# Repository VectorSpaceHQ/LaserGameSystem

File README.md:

# LaserGameSystem
A laser projector system which plays video games.

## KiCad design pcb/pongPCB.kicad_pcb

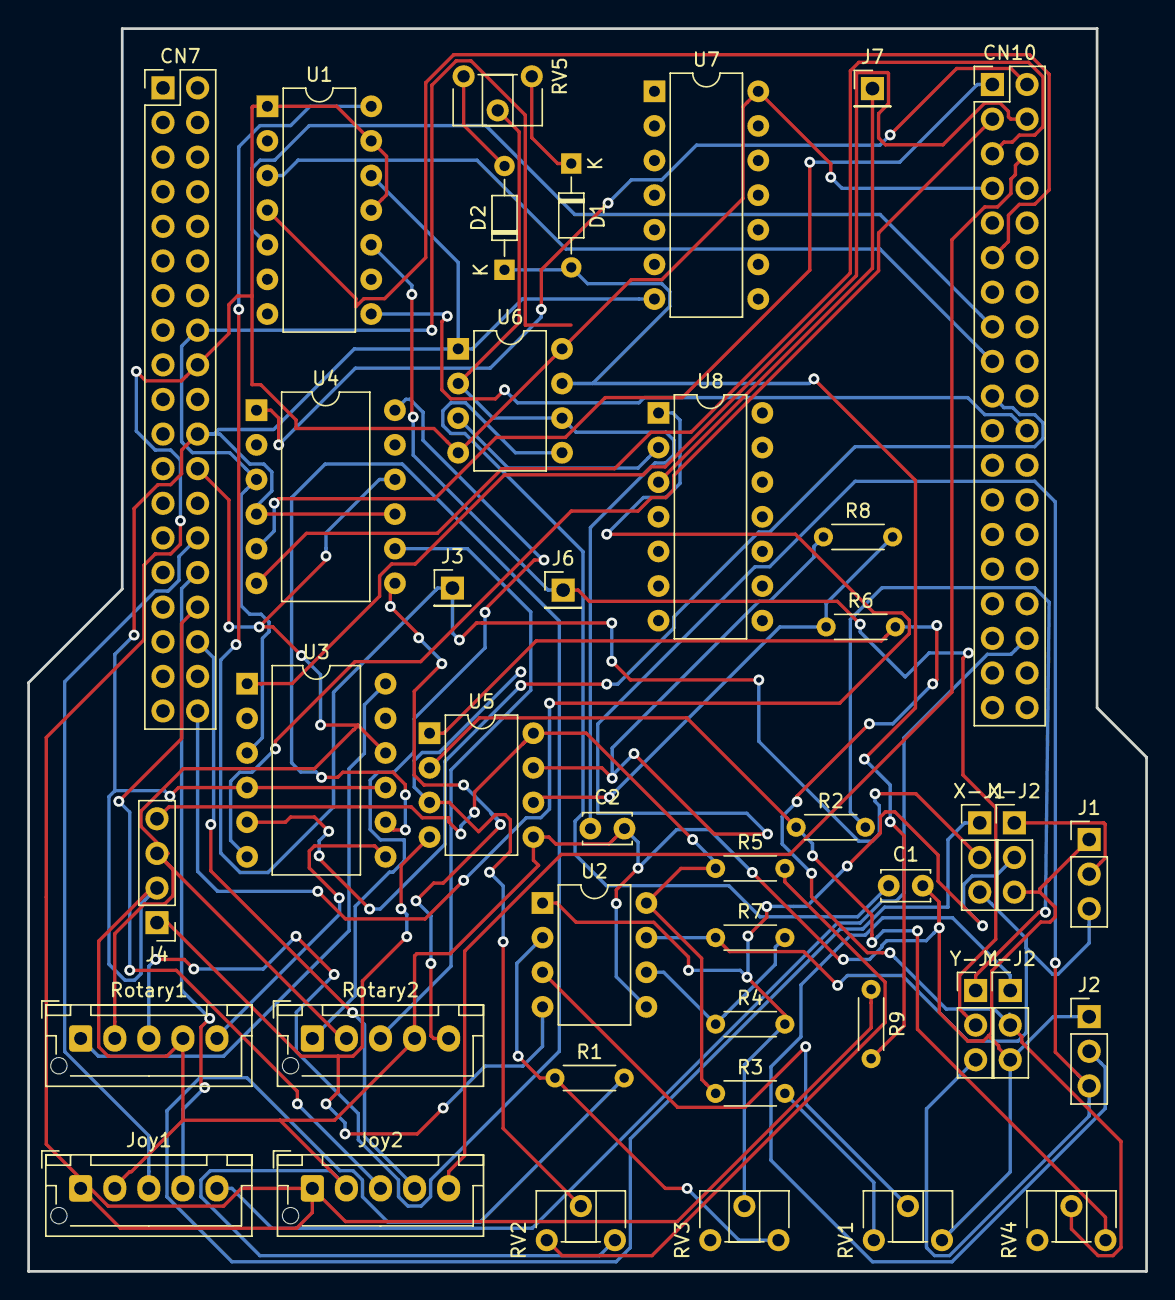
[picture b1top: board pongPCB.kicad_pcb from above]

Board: 2 copper layers, 82.0 x 91.2 mm, 42 parts (0 on the bottom side), 54 nets.

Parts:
C1: 104; C_Disc_D3.4mm_W2.1mm_P2.50mm
C2: 101; C_Disc_D3.4mm_W2.1mm_P2.50mm
CN7, CN10: Conn_02x19_Odd_Even; PinHeader_2x19_P2.54mm_Vertical
D1, D2: D; D_DO-34_SOD68_P7.62mm_Horizontal
J1: X_ILDA_OUT; PinHeader_1x03_P2.54mm_Vertical
J2: Y_ILDA_OUT; PinHeader_1x03_P2.54mm_Vertical
J3: Xprobe; PinHeader_1x01_P2.54mm_Vertical
J4: PowerInput; PinHeader_1x04_P2.54mm_Vertical
J6: Yprobe; PinHeader_1x01_P2.54mm_Vertical
J7: LaserToggle; PinHeader_1x01_P2.54mm_Vertical
Joy1, Joy2: Conn_01x05_Male; JST_XH_B05B-XH-AM_1x05_P2.50mm_Vertical
R1, R2: 1k; R_Axial_DIN0204_L3.6mm_D1.6mm_P5.08mm_Horizontal
R3, R5: 47k; R_Axial_DIN0204_L3.6mm_D1.6mm_P5.08mm_Horizontal
R4, R6, R7, R8: 10k; R_Axial_DIN0204_L3.6mm_D1.6mm_P5.08mm_Horizontal
R9: 2K; R_Axial_DIN0204_L3.6mm_D1.6mm_P5.08mm_Horizontal
RV1, RV2, RV3, RV4: 10k; Potentiometer_ACP_CA6-H2,5_Horizontal
RV5: 100K; Potentiometer_ACP_CA6-H2,5_Horizontal
Rotary1, Rotary2: Rotary_Encoder_Switch; JST_XH_B05B-XH-AM_1x05_P2.50mm_Vertical
U1: MCP4922; DIP-14_W7.62mm
U2, U5: TL082; DIP-8_W7.62mm
U3, U4: levelshift; DIP-12_W10.16mm
U6: NE555; DIP-8_W7.62mm
U7, U8: 4081; DIP-14_W7.62mm
X-J1: XJumper1; PinHeader_1x03_P2.54mm_Vertical
X-J2: XJumper2; PinHeader_1x03_P2.54mm_Vertical
Y-J1: YJumper1; PinHeader_1x03_P2.54mm_Vertical
Y-J2: YJumper2; PinHeader_1x03_P2.54mm_Vertical

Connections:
+3V3: CN7.16, U3.3, U4.3
+5V: CN7.18, CN10.7, Joy1.1, Joy2.1, R9.1, U1.1, U1.11, U1.13, U6.4, U6.8, U7.14
+12V: CN7.24, J4.3, Rotary1.2, Rotary2.2, U3.10, U4.10
+15V: J4.4, R3.1, R5.1, U2.8, U5.8
-15V: J4.1, U2.4, U5.4
/BUTTON1: CN10.3, U3.6
/BUTTON2: CN10.5, U4.6
/CLK1: CN10.19, U3.5
/CLK2: CN10.1, U4.5
/DT1: CN10.4, U3.1
/DT2: CN10.2, U4.1
/JOY1BUTTON: CN10.34, Joy1.5
/JOY1X: CN7.28, Joy1.3
/JOY1Y: CN7.30, Joy1.4
/JOY2BUTTON: CN10.6, Joy2.5
/JOY2X: CN7.32, Joy2.3
/JOY2Y: CN7.34, Joy2.4
/LASER_TOGGLE: CN7.38, U8.1
/LATCH: CN10.22, U1.8
GND: C1.2, C2.2, CN7.22, J1.1, J2.1, J4.2, Joy1.2, Joy2.2, RV1.3, RV2.3, Rotary1.4, Rotary2.4, U1.12, U2.5, U3.4, U3.9, U4.4, U4.9, U5.5, U6.1, U7.7, X-J2.3, Y-J2.3
unnamed: C1.1, U6.5
unnamed: C2.1, RV5.2, U6.2, U6.6
unnamed: CN10.11, U1.4
unnamed: CN10.15, U1.5
unnamed: CN10.17, U1.3
unnamed: D1.1, RV5.1
unnamed: D1.2, D2.1, R9.2, U6.7
unnamed: D2.2, RV5.3
unnamed: J1.2, X-J2.1
unnamed: J1.3, R7.1, U2.7, X-J1.3
unnamed: J2.2, Y-J2.1
unnamed: J2.3, R8.1, U5.7, Y-J1.3
unnamed: J3.1, U1.14, X-J1.2
unnamed: J6.1, U1.10, Y-J1.2
unnamed: J7.1, U8.3
unnamed: R1.1, RV3.3, U2.2
unnamed: R1.2, X-J1.1
unnamed: R2.1, RV4.3, U5.2
unnamed: R2.2, Y-J1.1
unnamed: R3.2, RV1.1
unnamed: R4.1, R7.2, U2.6
unnamed: R4.2, RV3.2, U2.1, X-J2.2
unnamed: R5.2, RV2.1
unnamed: R6.1, R8.2, U5.6
unnamed: R6.2, RV4.2, U5.1, Y-J2.2
unnamed: RV1.2, U2.3
unnamed: RV2.2, U5.3
unnamed: Rotary1.1, U3.12
unnamed: Rotary1.3, U3.8
unnamed: Rotary1.5, U3.7
unnamed: Rotary2.1, U4.12
unnamed: Rotary2.3, U4.8
unnamed: Rotary2.5, U4.7
unnamed: U6.3, U8.2

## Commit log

2019-01-18 Commit initial project tree.
2019-01-19 Fix Nucleo linker file location in build.
2019-01-19 Fix Nucleo HAL.
2019-01-19 GameSystem comes up and runs on the Nucleo board!
2019-01-19 Why use pointers?
2019-01-19 Update UML to document changes to Hal.
2019-01-19 Add settings directory to .gitignore
2019-01-20 Add PC platform with SDL library
2019-01-23 Construct Display and both programs (Calibrate and Pong).
2019-01-23 Game system is now running the calibrate program.
2019-01-23 Add DisplayImpl interface which the Display will call.
2019-01-23 Add Eigen to the project.
2019-01-23 Test Eigen integration into Calibrate program.
2019-01-26 Add uCOS-II
2019-01-28 Add basic Shape class using Eigen.
2019-01-28 Refactor DeviceImpl to DeviceIfc, and remove update function.
2019-01-28 Modify Calibrate to use the new Shape class.
2019-01-28 Rename Display to Canvas.
2019-01-28 Store original shape in Calibrate.
2019-01-28 Initialize backupVertices in Shape.
2019-02-01 First attempt to collect shape vertices in the Canvas and pass to the display.
2019-02-01 Rename LaserCanvas.cpp to LaserDisplay.cpp.
    (Not sure how it was renamed to Canvas to begin with)
2019-02-05 Fix bug in the Calibrat program which would always display the original shape instead of the scaled shape.
2019-02-05 Setup Game System Events for running programs.
2019-02-10 Change clock settings so that we get 84MHz system clock
2019-02-10 Integrate HAL support into game system
2019-02-10 Change VertexList_t array to two variables.
2019-02-10 TEMP: comment out HAL_TIM_Base_Start_IT() until the hardware timer can be fixed.
2019-02-10 Remove ScheduledInterval from Canvas.
2019-02-11 Stupid C++ name mangling
2019-02-11 Can't use board LED if we are using SPI...and need to add hal msp file
2019-02-12 Multiple shapes work, but have timing problem.
2019-02-13 New SVG Display project for generating SVG files.
2019-02-13 Add run time to GameSystem.
2019-02-13 SVGDisplay now writes to an SVG file.
2019-02-13 Fix output of SVG file "set" tag.
2019-02-14 Repeat the SVG animation.
2019-02-14 SVG: Adjust viewport to use the points as-is, without adjustment.
2019-02-15 Add common shapes including rectangle, square, polygon, and star.
2019-02-15 Add new abstract type CanvasObject.
2019-02-15 Add the Sprite class to handle multiple shapes, animation, and collision detection.
2019-02-15 Canvas now has a width and height.
2019-02-15 Animated shapes with collision detection on the border.
2019-02-16 Properly using Cartesian coordinate system now.
2019-02-16 Save some memory for now.
2019-02-16 Randomize speed of the various shapes.
2019-02-16 Why not two sprites?
2019-02-16 Decrease size of canvas to fix potential edge issues.
2019-02-17 Adjustments to memory allocation and usage.
2019-02-17 Reduce number of concurrent sets of vertices required.
2019-02-17 Calibration now has four sprites, each with it's own shape.
2019-02-17 initial commit of kicad pcb files.
2019-02-18 Split available memory between app stack and system heap.
    Apparently, some mallocs come from the system heap, and others from the
    app task stack. Not quite sure which ones.
2019-02-18 Remove Eigen arrays from LaserDisplay.
    Reduces memory usage in the display by 2/3, and reduces load on the
    interrupt routine.
2019-02-18 Only reserve memory for Shape::backupVertices if explicitly requested to make a backup.
2019-02-18 Smaller shapes look cooler!
2019-02-19 Move the shapes from the Calibrate program to the Test Program.
2019-02-19 Add a new cursor shape.
2019-02-19 Start of the Calibration program. Now need joystick input.
2019-02-19 Move some things into the GameSystem namespace.
2019-02-19 Pong has started!
2019-02-20 Add NumeralShape and scores to GiantPong.
2019-02-20 worked with Jordan to implement Nucleo shield.
2019-02-20 finished pcb layout. Ready for review
2019-02-20 added edge cuts
2019-02-20 Added drill files
2019-02-23 Pong game board is running on the laser.
2019-02-23 Missed file from previous commit.
2019-02-24 Turn laser on/off
2019-02-26 Fix memory issue
2019-02-26 state of PCB at time of first order
2019-02-28 Sprite limits are now working, although the X-axis limit may be inverted.
2019-02-28 Invert limits so they make logical sense.
2019-02-28 Make a little better use of Eigen.
2019-02-28 Sprite-to-sprite collision detection is working.
2019-03-01 Add some error to the sprite collision detection.
2019-03-01 Beginnings of a GiantPong splash screen.
2019-03-10 Implement Finite State Machine for GiantPong.
2019-03-10 Fix compilation issue on PC SVG for MacOS X.
2019-03-11 Fix some paddle/ball collision detection problems.
2019-03-11 Implement GianPong demo mode.
2019-03-11 Player can now click to start the game (or auto-start if computer is playing).
2019-03-11 Some Pong game play additions and improvements.
2019-03-11 Refactor Paddles to Players and Ball.
2019-03-12 Bypass the splash screen, and fix re-initialization problem.
2019-03-12 Fill out GamePad interface class.
2019-03-12 Add GetId() to GamePad.
2019-03-12 GamePads build for PC SVG.
2019-03-12 Update LaserDisplay for new hardware.
2019-03-12 Add Nucleo paddles
2019-03-12 Blank laser when not in use, and auto-restart game for now.
2019-03-12 Tweak button handling
2019-03-17 Add Player Select screen.
2019-03-18 Reduce point count in "GIANT" splashscreen.
2019-03-18 Move "GIANT" text points to const array.
2019-03-19 Some debugging and game improvements.
2019-03-19 Add the Game Over screen
2019-03-19 Add constant for paddle speed.
2019-03-19 Added simplified "PONG" splash screen.
2019-03-19 Remove paddle track error during demo mode.
2019-03-19 Fix paddle wrap-around from top to bottom.
2019-03-20 Players can adjust the speed of the ball.
    And other configuration changes.
